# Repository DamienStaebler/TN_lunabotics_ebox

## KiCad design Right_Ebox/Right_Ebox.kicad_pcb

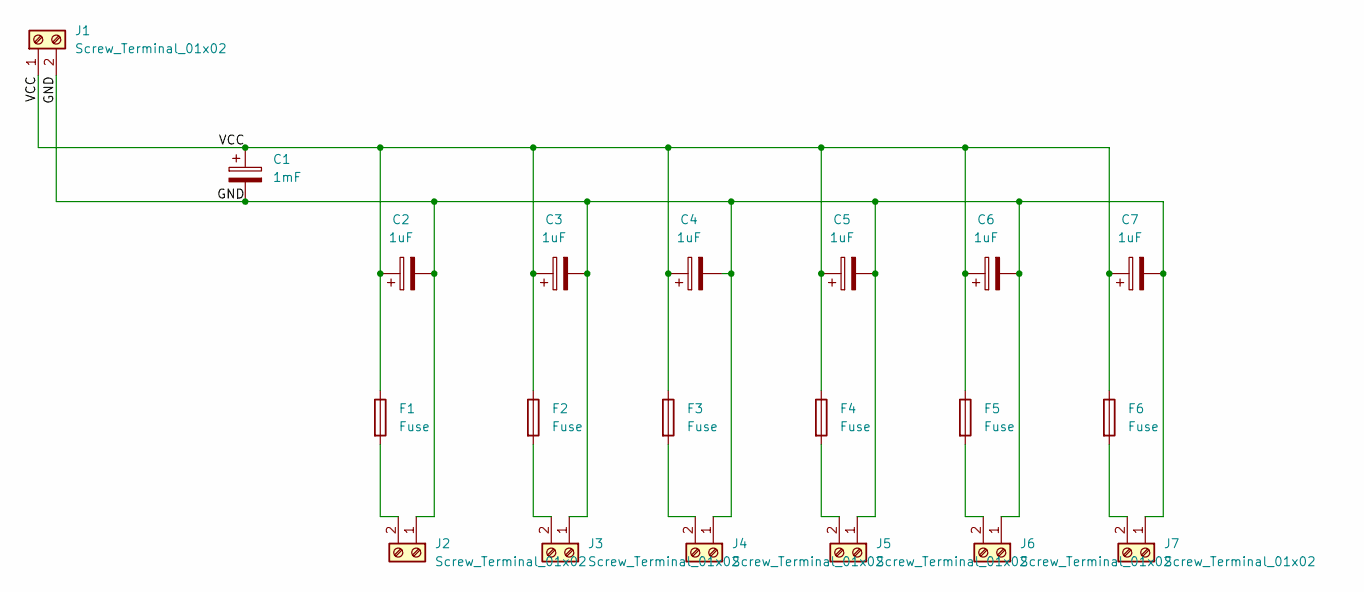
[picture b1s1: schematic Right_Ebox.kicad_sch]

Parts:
C1: 1mF; CP_Radial_D8.0mm_P3.80mm
C2, C3, C4, C5, C6, C7: 1uF; CP_Radial_D5.0mm_P2.50mm
F1, F2, F3, F4, F5, F6: Fuse; FUSE
J1: Screw_Terminal_01x02; BATTERY_AND_LOW_VOLTAGE_CONNECTOR
J2, J3, J4, J5, J6, J7: Screw_Terminal_01x02; SPARMAX_CONN

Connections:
/GND: C1.2, C2.2, C3.2, C4.2, C5.2, C6.2, C7.2, J1.2, J2.1, J3.1, J4.1, J5.1, J6.1, J7.1
/VCC: C1.1, C2.1, C3.1, C4.1, C5.1, C6.1, C7.1, F1.1, F2.1, F3.1, F4.1, F5.1, F6.1, J1.1
unnamed: F1.2, J2.2
unnamed: F2.2, J3.2
unnamed: F3.2, J4.2
unnamed: F4.2, J5.2
unnamed: F5.2, J6.2
unnamed: F6.2, J7.2

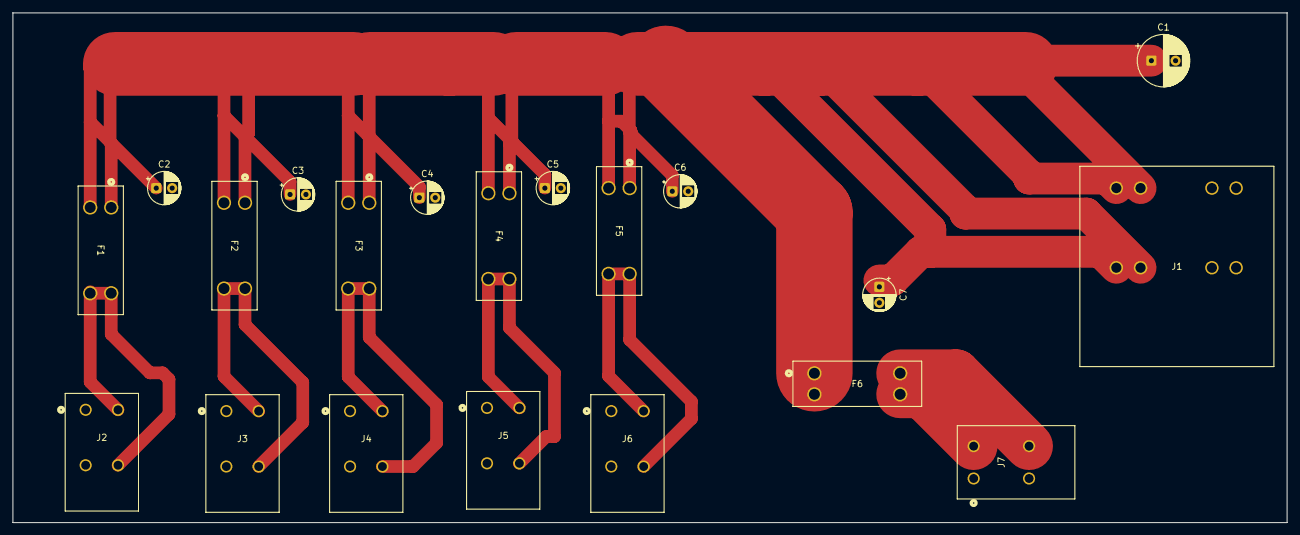
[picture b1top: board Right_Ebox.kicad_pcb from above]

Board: 2 copper layers, 200.0 x 80.0 mm, 20 parts (0 on the bottom side), 8 nets.
